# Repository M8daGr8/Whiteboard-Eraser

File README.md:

# Whiteboard Eraser
Joystick controlled whiteboard eraser.

## Joystick
### PCB

### CAD

## Eraser
### PCB

### CAD

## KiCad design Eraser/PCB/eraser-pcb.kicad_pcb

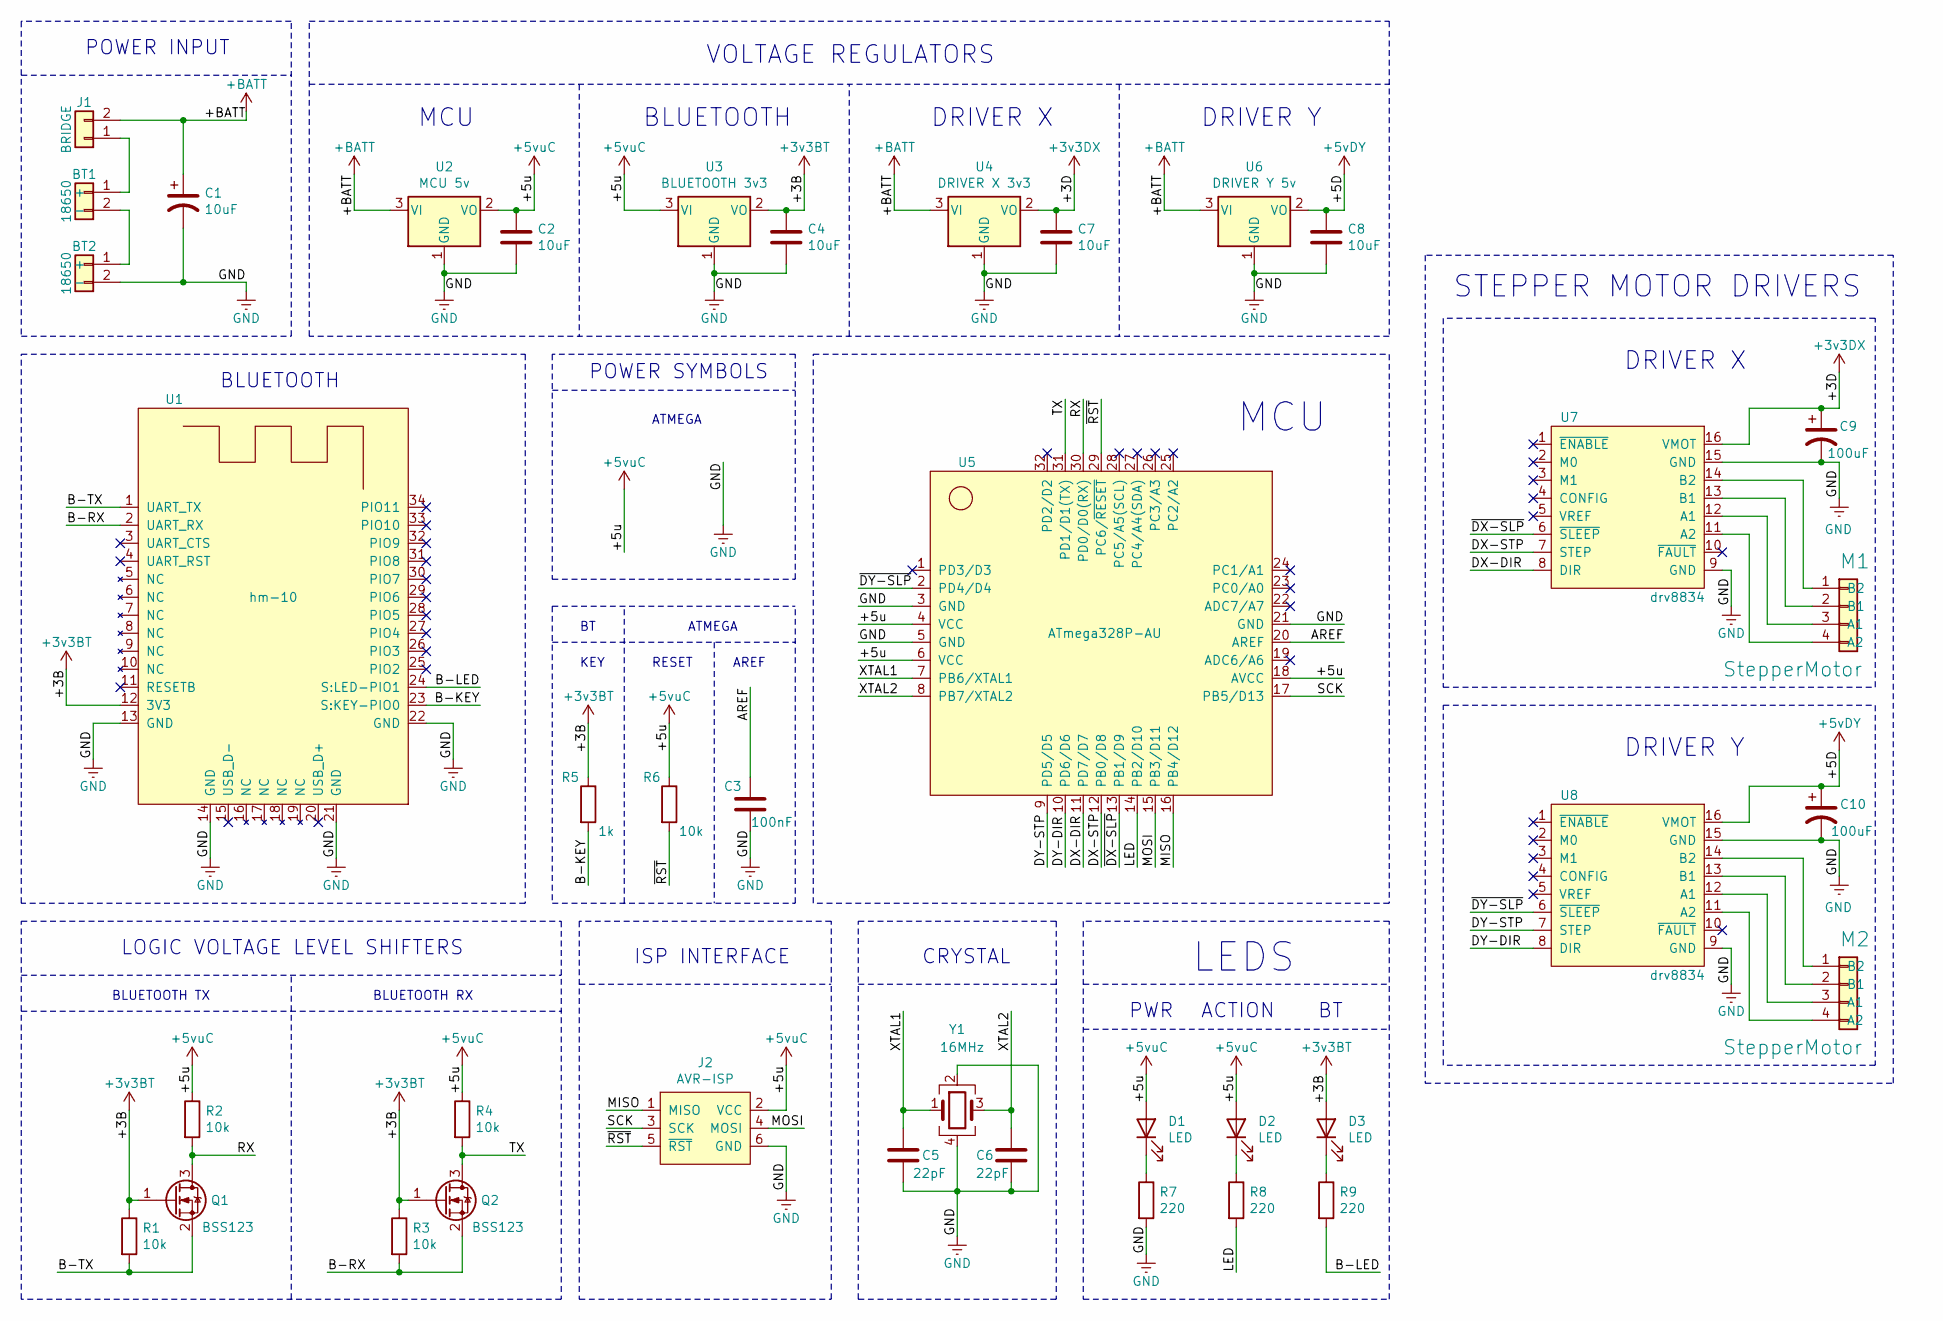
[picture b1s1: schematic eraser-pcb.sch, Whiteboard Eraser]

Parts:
BT1, BT2: 18650; JST_PH_S2B-PH-SM4-TB_1x02-1MP_P2.00mm_Horizontal
C1: 10uF; CP_EIA-6032-28_Kemet-C_Pad2.25x2.35mm_HandSolder
C2, C4, C7, C8: 10uF; C_0805_2012Metric_Pad1.15x1.40mm_HandSolder
C3: 100nF; C_0805_2012Metric_Pad1.15x1.40mm_HandSolder
C5, C6: 22pF; C_0805_2012Metric_Pad1.15x1.40mm_HandSolder
C9, C10: 100uF; CP_Elec_5x5.3
D1, D2, D3: LED; LED_0805_2012Metric_Pad1.15x1.40mm_HandSolder
J1: BRIDGE; PinHeader_1x02_P2.54mm_Vertical
J2: AVR-ISP; IDC-Header_2x03_P2.54mm_Vertical
M1, M2: StepperMotor; JST_XH_B4B-XH-A_1x04_P2.50mm_Vertical
Q1, Q2: BSS123; SOT-23
R1, R2, R3, R4, R6: 10k; R_0805_2012Metric_Pad1.15x1.40mm_HandSolder
R5: 1k; R_0805_2012Metric_Pad1.15x1.40mm_HandSolder
R7, R8, R9: 220; R_0805_2012Metric_Pad1.15x1.40mm_HandSolder
U1: hm-10
U2: MCU 5v; SOT-223-3_TabPin2
U3: BLUETOOTH 3v3; SOT-223-3_TabPin2
U4: DRIVER X 3v3; SOT-223-3_TabPin2
U5: ATmega328P-AU; TQFP-32_7x7mm_P0.8mm
U6: DRIVER Y 5v; SOT-223-3_TabPin2
U7, U8: drv8834
Y1: 16MHz; CFPX_104-5x3.2mm

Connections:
+BATT: C1.1, J1.2, U2.3 (VI), U4.3 (VI), U6.3 (VI)
/+3B: C4.1, D3.2 (A), Q1.1 (G), Q2.1 (G), R1.1, R3.1, R5.1, U1.12 (3V3), U3.2 (VO)
/+3D: C7.1, C9.1, U4.2 (VO), U7.16 (VMOT)
/+5D: C8.1, C10.1, U6.2 (VO), U8.16 (VMOT)
/+5u: C2.1, D1.2 (A), D2.2 (A), J2.2 (VCC), R2.1, R4.1, R6.1, U2.2 (VO), U3.3 (VI), U5.4 (VCC), U5.6 (VCC), U5.18 (AVCC)
/AREF: C3.1, U5.20 (AREF)
/B-KEY: R5.2, U1.23 (S:KEY-PIO0)
/B-LED: R9.2, U1.24 (S:LED-PIO1)
/B-RX: Q2.2 (S), R3.2, U1.2 (UART_RX)
/B-TX: Q1.2 (S), R1.2, U1.1 (UART_TX)
/DA-DIR: U5.11 (PD7/D7), U7.8 (DIR)
/DA-STP: U5.12 (PB0/D8), U7.7 (STEP)
/DB-DIR: U5.10 (PD6/D6), U8.8 (DIR)
/DB-STP: U5.9 (PD5/D5), U8.7 (STEP)
/GND: BT1.MP, BT2.2 (-), BT2.MP, C1.2, C2.2, C3.2, C4.2, C5.2, C6.2, C7.2, C8.2, C9.2, C10.2, J2.6 (GND), R7.2, U1.13 (GND), U1.14 (GND), U1.21 (GND), U1.22 (GND), U2.1 (GND), U3.1 (GND), U4.1 (GND), U5.3 (GND), U5.5 (GND), U5.21 (GND), U6.1 (GND), U7.9 (GND), U7.15 (GND), U8.9 (GND), U8.15 (GND), Y1.2, Y1.4
/LED: R8.2, U5.14 (PB2/D10)
/MISO: J2.1 (MISO), U5.16 (PB4/D12)
/MOSI: J2.4 (MOSI), U5.15 (PB3/D11)
/RX: Q1.3 (D), R2.2, U5.30 (PD0/D0(RX))
/SCK: J2.3 (SCK), U5.17 (PB5/D13)
/TX: Q2.3 (D), R4.2, U5.31 (PD1/D1(TX))
/XTAL1: C5.1, U5.7 (PB6/XTAL1), Y1.1
/XTAL2: C6.1, U5.8 (PB7/XTAL2), Y1.3
/~DA-SLP: U5.13 (PB1/D9), U7.6 (~SLEEP)
/~DB-SLP: U5.2 (PD4/D4), U8.6 (~SLEEP)
/~RST: J2.5 (~RST), R6.2, U5.29 (PC6/~RESET~)
unnamed: BT1.1 (+), J1.1
unnamed: BT1.2 (-), BT2.1 (+)
unnamed: D1.1 (K), R7.1
unnamed: D2.1 (K), R8.1
unnamed: D3.1 (K), R9.1
unnamed: M1.1 (B2), U7.14 (B2)
unnamed: BT2.MP, M1.2 (B1), U7.13 (B1)
unnamed: M1.3 (A1), U7.12 (A1)
unnamed: M1.4 (A2), U7.11 (A2)
unnamed: M2.1 (B2), U8.14 (B2)
unnamed: M2.2 (B1), U8.13 (B1)
unnamed: BT1.MP, M2.3 (A1), U8.12 (A1)
unnamed: M2.4 (A2), U8.11 (A2)

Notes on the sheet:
PWR
ACTION
BLUETOOTH
LEDS
MCU
DRIVER Y
STEPPER MOTOR DRIVERS
DRIVER X
POWER INPUT
VOLTAGE REGULATORS
ISP INTERFACE
RESET
CRYSTAL
ATMEGA
POWER SYMBOLS
KEY
AREF
LOGIC VOLTAGE LEVEL SHIFTERS
BLUETOOTH RX
BLUETOOTH TX

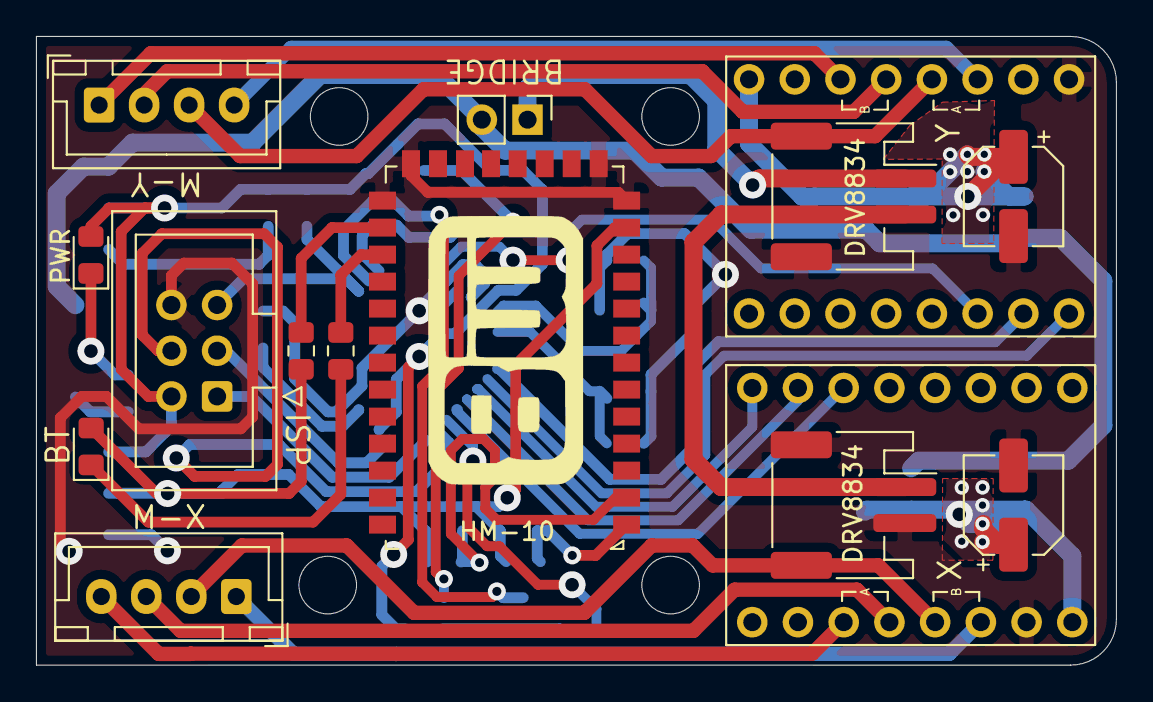
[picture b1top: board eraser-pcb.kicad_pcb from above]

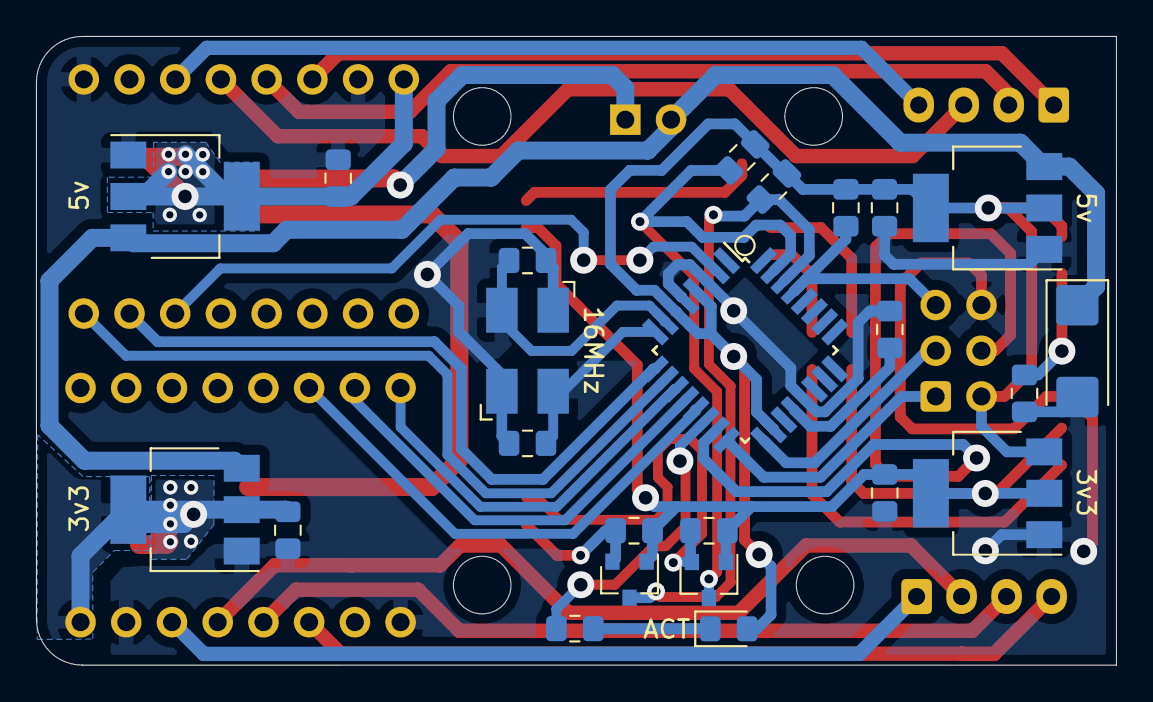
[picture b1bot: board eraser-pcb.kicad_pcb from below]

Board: 2 copper layers, 60.0 x 34.9 mm, 39 parts (24 on the bottom side), 39 nets.

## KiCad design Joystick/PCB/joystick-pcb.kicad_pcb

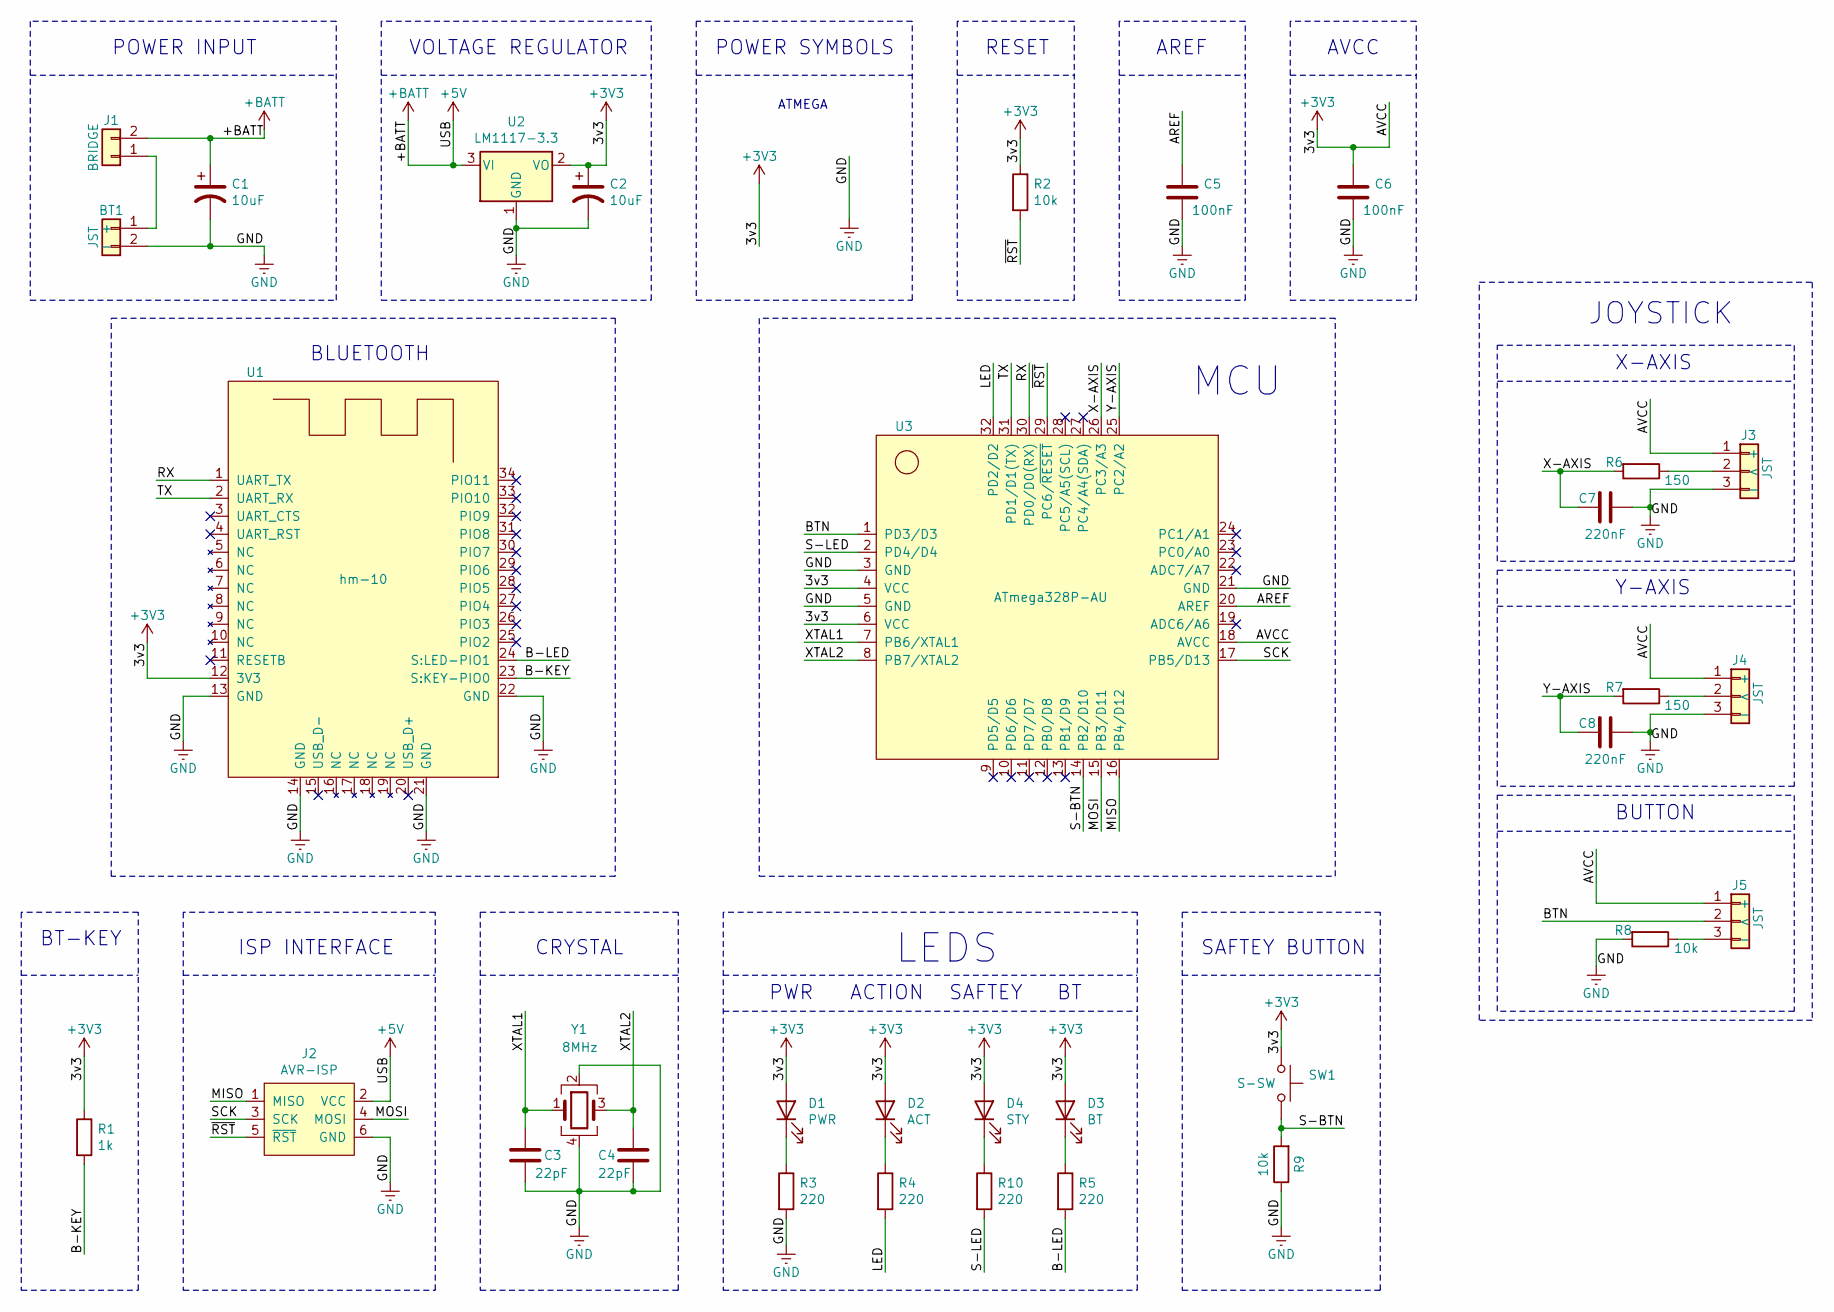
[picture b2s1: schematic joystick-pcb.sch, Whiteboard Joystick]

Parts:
BT1: JST; JST_PH_S2B-PH-SM4-TB_1x02-1MP_P2.00mm_Horizontal
C1, C2: 10uF; CP_EIA-6032-28_Kemet-C_Pad2.25x2.35mm_HandSolder
C3, C4: 22pF; C_0805_2012Metric_Pad1.15x1.40mm_HandSolder
C5, C6: 100nF; C_0805_2012Metric_Pad1.15x1.40mm_HandSolder
C7, C8: 220nF; C_0805_2012Metric_Pad1.15x1.40mm_HandSolder
D1: PWR; LED_0805_2012Metric_Pad1.15x1.40mm_HandSolder
D2: ACT; LED_0805_2012Metric_Pad1.15x1.40mm_HandSolder
D3: BT; LED_0805_2012Metric_Pad1.15x1.40mm_HandSolder
D4: STY; LED_0805_2012Metric_Pad1.15x1.40mm_HandSolder
J1: BRIDGE; PinHeader_1x02_P2.54mm_Vertical
J2: AVR-ISP; IDC-Header_2x03_P2.54mm_Vertical
J3, J4, J5: JST; JST_PH_S3B-PH-K_1x03_P2.00mm_Horizontal
R1: 1k; R_0805_2012Metric_Pad1.15x1.40mm_HandSolder
R2, R8, R9: 10k; R_0805_2012Metric_Pad1.15x1.40mm_HandSolder
R3, R4, R5, R10: 220; R_0805_2012Metric_Pad1.15x1.40mm_HandSolder
R6, R7: 150; R_0805_2012Metric_Pad1.15x1.40mm_HandSolder
SW1: S-SW; SW_Tactile_SPST_Angled_PTS645Vx39-2LFS
U1: hm-10
U2: LM1117-3.3; SOT-223-3_TabPin2
U3: ATmega328P-AU; TQFP-32_7x7mm_P0.8mm
Y1: 8MHz; CFPX_104-5x3.2mm

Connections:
+3V3: C2.1, C6.1, D1.2 (A), D2.2 (A), D3.2 (A), D4.2 (A), J3.1 (+), J4.1 (+), J5.1 (+), R1.1, R2.1, SW1.1, U1.12 (3V3), U2.2 (VO), U3.4 (VCC), U3.6 (VCC), U3.18 (AVCC)
+5V: C1.1, J1.2, J2.2 (VCC), U2.3 (VI)
/AREF: C5.1, U3.20 (AREF)
/B-KEY: R1.2, U1.23 (S:KEY-PIO0)
/B-LED: R5.2, U1.24 (S:LED-PIO1)
/BTN: J5.2 (<), U3.1 (PD3/D3)
/GND: BT1.2 (-), C1.2, C2.2, C3.2, C4.2, C5.2, C6.2, C7.1, C8.1, J2.6 (GND), J3.3 (-), J4.3 (-), R3.2, R8.2, R9.1, U1.13 (GND), U1.14 (GND), U1.21 (GND), U1.22 (GND), U2.1 (GND), U3.3 (GND), U3.5 (GND), U3.21 (GND), Y1.2, Y1.4
/LED: R4.2, U3.32 (PD2/D2)
/MISO: J2.1 (MISO), U3.16 (PB4/D12)
/MOSI: J2.4 (MOSI), U3.15 (PB3/D11)
/RX: U1.1 (UART_TX), U3.30 (PD0/D0(RX))
/S-BTN: R9.2, SW1.2, U3.14 (PB2/D10)
/S-LED: R10.2, U3.2 (PD4/D4)
/SCK: J2.3 (SCK), U3.17 (PB5/D13)
/TX: U1.2 (UART_RX), U3.31 (PD1/D1(TX))
/X-AXIS: C7.2, R6.2, U3.26 (PC3/A3)
/XTAL1: C3.1, U3.7 (PB6/XTAL1), Y1.1
/XTAL2: C4.1, U3.8 (PB7/XTAL2), Y1.3
/Y-AXIS: C8.2, R7.2, U3.25 (PC2/A2)
/~RST: J2.5 (~RST), R2.2, U3.29 (PC6/~RESET~)
unnamed: BT1.1 (+), J1.1
unnamed: D1.1 (K), R3.1
unnamed: D2.1 (K), R4.1
unnamed: D3.1 (K), R5.1
unnamed: D4.1 (K), R10.1
unnamed: J3.2 (<), R6.1
unnamed: J4.2 (<), R7.1
unnamed: J5.3 (-), R8.1

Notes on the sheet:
CRYSTAL
POWER INPUT
VOLTAGE REGULATOR
ISP INTERFACE
LEDS
POWER SYMBOLS
ATMEGA
PWR
ACTION
BT-KEY
AREF
RESET
JOYSTICK
X-AXIS
MCU
BLUETOOTH
AVCC
SAFTEY BUTTON
SAFTEY
Y-AXIS
BUTTON

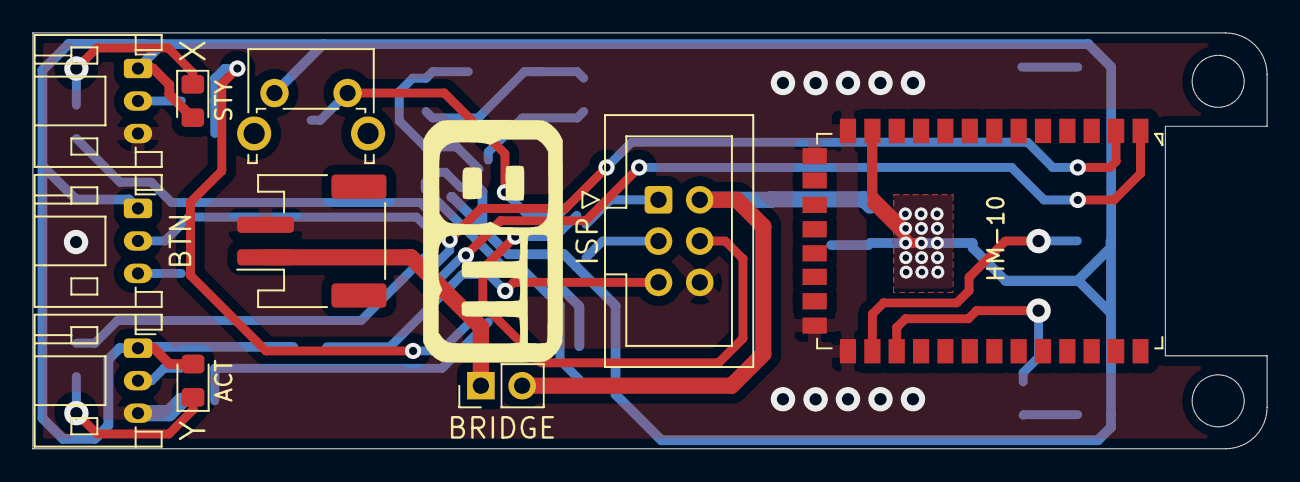
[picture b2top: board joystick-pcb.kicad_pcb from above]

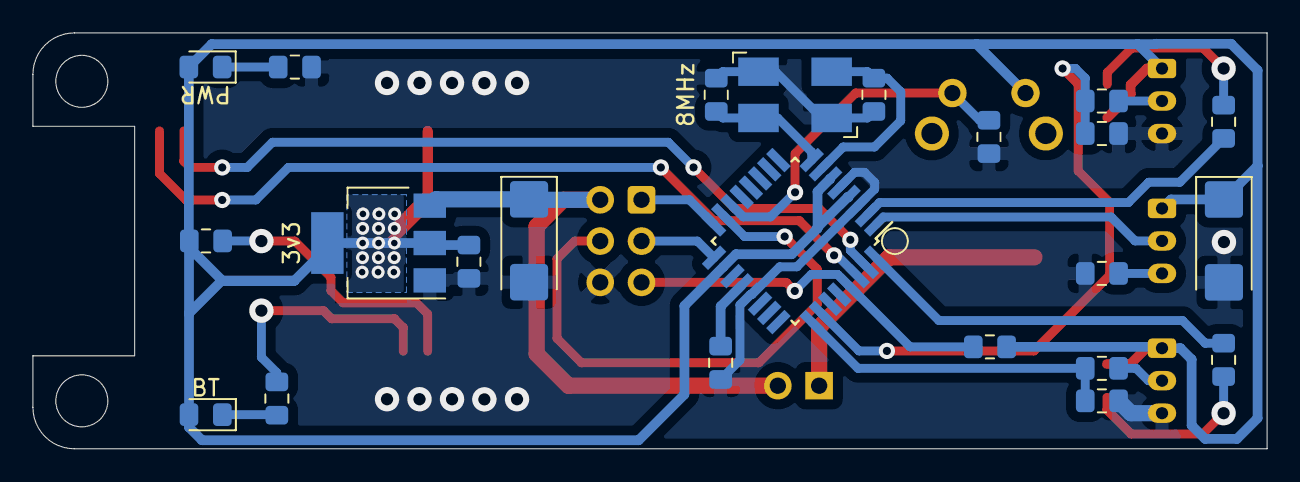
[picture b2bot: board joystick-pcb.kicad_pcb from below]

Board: 2 copper layers, 75.9 x 25.6 mm, 33 parts (23 on the bottom side), 28 nets.

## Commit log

2020-11-18 Init commit
2020-11-18 changes in code. Added comment and changed eraser timer interrupt
